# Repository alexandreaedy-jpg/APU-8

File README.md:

# APU-8

APU-8 is an experimental MIDI-controlled NES instrument project.

The repository now exposes the active V2 expansion-port build first, and keeps older iterations in `Archive/`.

## Current active target

- Current ROM source: `ROM V2B\v2b_step5ar_flat_env_pitch`
- Current ROM output: `ROM V2B\v2b_step5ar_flat_env_pitch\V2_MIDI_IN_P1P2.nes`
- Current Pico sketch: `Firmware Arduino\Firmware_PICO-V2B`
- Current Pico firmware string in the sketch: `FW=t84-v2b-step5bb-groovejitter`
- Last fully documented accepted milestone: `FW=t79-v2b-step5aw-wavefix`

Quick commands:

```powershell
.\tools\v2.cmd status midi
.\tools\v2.cmd build-rom midi
.\tools\v2.cmd build-pico midi
.\tools\v2.cmd deploy midi
```

For a direct overview, start with [CURRENT_TARGETS.md](CURRENT_TARGETS.md).

## Repository layout

```text
APU-8/
|-- ROM V2B/                          # current ROM source tree
|   `-- v2b_step5ar_flat_env_pitch/
|-- Firmware Arduino/                 # current Pico sketch + diagnostics
|   |-- Firmware_PICO-V2B/
|   |-- PicoMcp3008RawDiag/
|   `-- PicoPanelCtrlFullDiag/
|-- Archive/                          # archived ROM/sketch history and legacy branches
|   |-- Project-V2-A/
|   |-- arduino/
|   `-- legacy-root/
|-- hardware/                         # KiCad / PCB work
|-- max-for-live/                     # control tooling
|-- milestones/                       # frozen milestone snapshots
`-- tools/                            # build / flash shortcuts
```

## What moved to Archive

- Older `Project-V2-A` step folders
- Older Arduino Nano / Pico sketches
- Legacy controller-port ROM branches and side experiments

The build shortcuts were kept alive:

- `midi` now targets the current active build
- `midi-v2a` points to the archived V2A baseline
- `midi-v2b1` to `midi-v2b21` still point to their archived step folders
- `midi-v2b22` explicitly points to the current Step5AR folder

## Important files

- [CURRENT_TARGETS.md](CURRENT_TARGETS.md)
- [PROJECT_STATE.md](PROJECT_STATE.md)
- [SHORT_COMMANDS.md](SHORT_COMMANDS.md)
- [ROM V2B/V2B_STEP5AR_FLAT_ENV_PITCH_2026-05-28.md](ROM%20V2B/V2B_STEP5AR_FLAT_ENV_PITCH_2026-05-28.md)
- [hardware/APU8_V2B_KICAD/README.md](hardware/APU8_V2B_KICAD/README.md)

## Notes

- The active ROM folder is still named `v2b_step5ar_flat_env_pitch`, but the paired Pico sketch continued past the original Step5AR note and now reports `t84-v2b-step5bb-groovejitter`.
- `PROJECT_STATE.md` remains the long-form engineering journal.
- `Archive/` keeps history accessible without leaving the root crowded.

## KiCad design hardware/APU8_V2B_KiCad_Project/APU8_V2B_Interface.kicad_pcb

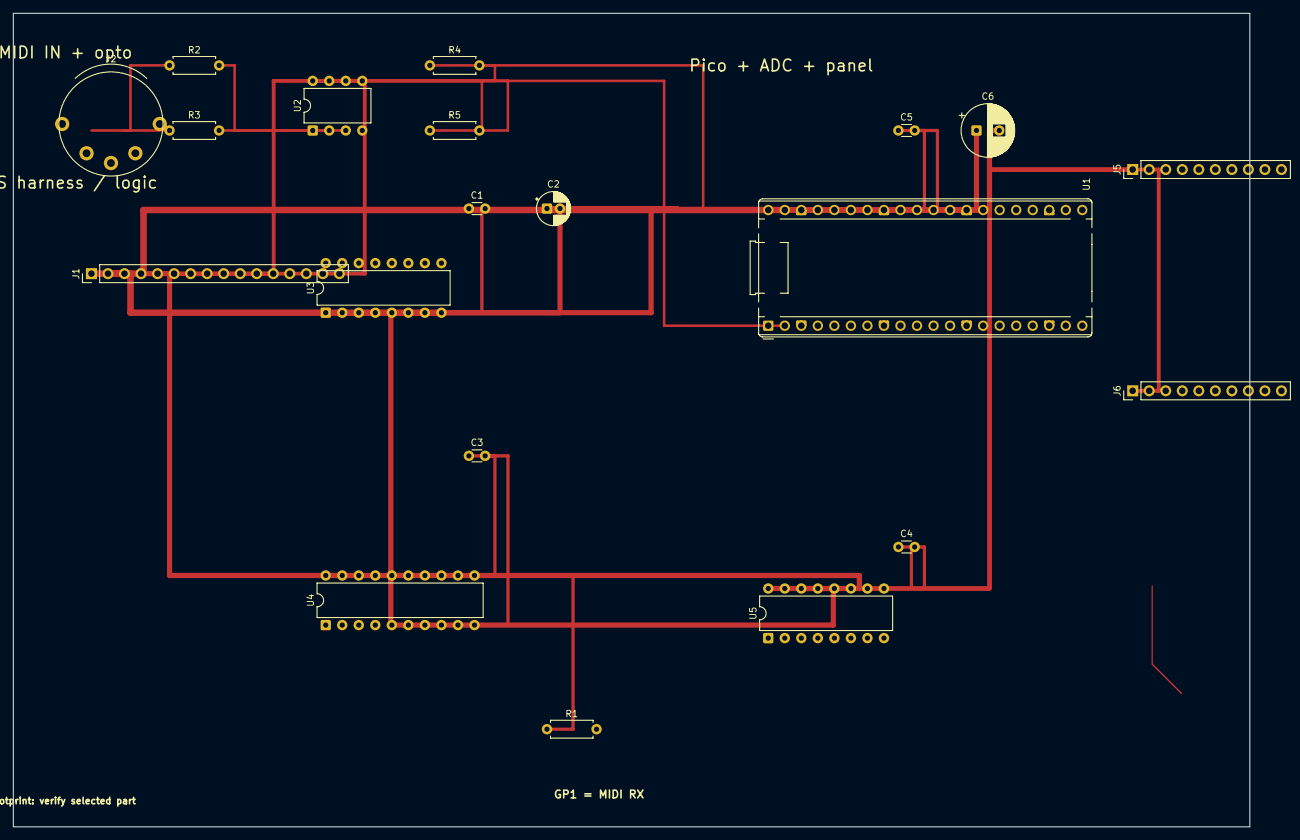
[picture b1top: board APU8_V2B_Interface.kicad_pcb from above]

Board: 2 copper layers, 190.0 x 125.0 mm, 20 parts (0 on the bottom side), 51 nets.

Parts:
C1: 100n 3V3; C_Disc_D3.0mm_W1.6mm_P2.50mm
C2: 10u 3V3; CP_Radial_D5.0mm_P2.00mm
C3: 100n 5V HC245; C_Disc_D3.0mm_W1.6mm_P2.50mm
C4: 100n 5V MCP; C_Disc_D3.0mm_W1.6mm_P2.50mm
C5: 100n 5V bulk local; C_Disc_D3.0mm_W1.6mm_P2.50mm
C6: 47u 5V; CP_Radial_D8.0mm_P3.50mm
J1: NES_HARNESS; PinHeader_1x16_P2.54mm_Vertical
J2: MIDI_DIN_IN; DIN5_180_Placeholder_THT
J5: PANEL_ANALOG; PinHeader_1x10_P2.54mm_Vertical
J6: PANEL_SWITCHES; PinHeader_1x10_P2.54mm_Vertical
R1: 10k; R_Axial_DIN0207_L6.3mm_D2.5mm_P7.62mm_Horizontal
R2, R3: 220R; R_Axial_DIN0207_L6.3mm_D2.5mm_P7.62mm_Horizontal
R4: 4k7; R_Axial_DIN0207_L6.3mm_D2.5mm_P7.62mm_Horizontal
R5: 1k; R_Axial_DIN0207_L6.3mm_D2.5mm_P7.62mm_Horizontal
U1: RaspberryPi_Pico; RaspberryPi_Pico_Common_THT
U2: 6N138; DIP-8_W7.62mm
U3: 74HC4050; DIP-16_W7.62mm
U4: 74HCT245; DIP-20_W7.62mm
U5: MCP3008; DIP-16_W7.62mm

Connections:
3V3: C1.1, C2.1, R4.1, U1.36, U3.1
+5V: C3.1, C4.1, C5.1, C6.1, J1.1, J5.1, R1.1, U1.39, U2.8, U4.1, U4.20, U5.15, U5.16
A15_OPTIONAL: J1.13, U3.11
GND: C1.2, C2.2, C3.2, C4.2, C5.2, C6.2, J1.2, J1.3, J5.2, J6.1, R5.2, U1.3, U1.8, U1.13, U1.18, U1.23, U1.28, U1.33, U1.38, U2.5, U3.8, U4.10, U5.9, U5.14
GP2_OUT0: U1.4, U3.2
GP3_OUT1: U1.5, U3.4
GP4_OUT2: U1.6, U3.6
GP5_OE2_N: U1.7, U3.10
GP6_A15: U1.9, U3.12
GP10_D0: U1.14, U4.2
GP11_D1: U1.15, U4.3
GP12_D2: U1.16, U4.4
GP13_D3: U1.17, U4.5
GP14_D4: U1.19, U4.6
GP16_MISO: U1.21, U5.12
GP17_CS: U1.22, U5.10
GP18_SCK: U1.24, U5.13
GP19_MOSI: U1.25, U5.11
HCT245_OE_N: R1.2, U1.10, U4.19
MIDI_LED_A: R2.2, U2.2
MIDI_LED_K: R3.2, U2.3
MIDI_PIN4: J2.4, R2.1
MIDI_PIN5: J2.5, R3.1
MIDI_RX: R4.2, U1.2, U2.6
MIDI_SPEED: R5.1, U2.7
OE2_N: J1.7, U3.9
OUT0: J1.6, U3.3
OUT1: J1.5, U3.5
OUT2: J1.4, U3.7
PORT1_0: J1.8, U4.18
PORT1_1: J1.9, U4.17
PORT1_2: J1.10, U4.16
PORT1_3: J1.11, U4.15
PORT1_4: J1.12, U4.14
POT_ARP_TIME_OR_WAVE: J5.10, U5.8
POT_ATTACK: J5.3, U5.1
POT_DECAY: J5.5, U5.3
POT_DUTY_OR_TIMBRE: J5.9, U5.7
POT_LFO_DEPTH: J5.7, U5.5
POT_LFO_RATE: J5.8, U5.6
POT_RELEASE: J5.6, U5.4
POT_VOLUME: J5.4, U5.2
SW_ARP: J6.10, U1.34
SW_GLOBAL: J6.9, U1.32
SW_LFO_AMP: J6.4, U1.20
SW_LFO_DUTY: J6.3, U1.12
SW_LFO_PITCH: J6.2, U1.11
SW_NOISE: J6.8, U1.31
SW_P1: J6.5, U1.26
SW_P2: J6.6, U1.27
SW_TRI: J6.7, U1.29

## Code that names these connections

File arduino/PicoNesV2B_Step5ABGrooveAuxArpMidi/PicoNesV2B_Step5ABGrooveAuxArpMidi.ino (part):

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// - global duty + ADSR
// Goal: drive P1/P2/TRI directly from DIN MIDI on GP1, using the V18 channel map.

static const uint8_t PIN_MIDI_RX = 1;
static const uint8_t PIN_OUT0 = 2;
static const uint8_t PIN_OUT1 = 3;
static const uint8_t PIN_OUT2 = 4;
static const uint8_t PIN_OE2 = 5;
static const uint8_t PIN_A15 = 6;

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static const uint8_t kArpClocksPerStep[4] = {24U, 12U, 6U, 3U};

static inline uint8_t readOutBits() {
  return (uint8_t)((digitalRead(PIN_OUT0) ? 1 : 0) |
                   (digitalRead(PIN_OUT1) ? 2 : 0) |
                   (digitalRead(PIN_OUT2) ? 4 : 0));
}

static inline bool pinConfigured(uint8_t pin) {
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}

static void setupOutInputs() {
  pinMode(PIN_OUT0, INPUT);
  pinMode(PIN_OUT1, INPUT);
  pinMode(PIN_OUT2, INPUT);
  if (pinConfigured(PIN_OE2)) pinMode(PIN_OE2, INPUT);
  if (pinConfigured(PIN_A15)) pinMode(PIN_A15, INPUT);
  if (pinConfigured(PIN_CPU_D0)) pinMode(PIN_CPU_D0, INPUT);
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  writePattern(STATUS_IDLE_PATTERN);

  Serial.begin(115200);
  Serial1.setRX(PIN_MIDI_RX);
  Serial1.begin(MIDI_BAUD);
  delay(250);
  Serial.println();
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
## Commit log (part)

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2026-05-04 Initial commit APU8 v16 to v18
2026-05-04 README.md
